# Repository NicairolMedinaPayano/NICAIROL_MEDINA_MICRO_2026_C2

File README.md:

# NICAIROL_MEDINA_MICRO_2026_C2
Repositorio donde iré desarrollando y guardando proyectos y prácticas de microcontroladores, enfocados en programación embebida, automatización y sistemas electrónicos aplicados al área de Mecatrónica. Aquí estarán organizados los códigos, pruebas y avances realizados durante el proceso de aprendizaje y desarrollo.

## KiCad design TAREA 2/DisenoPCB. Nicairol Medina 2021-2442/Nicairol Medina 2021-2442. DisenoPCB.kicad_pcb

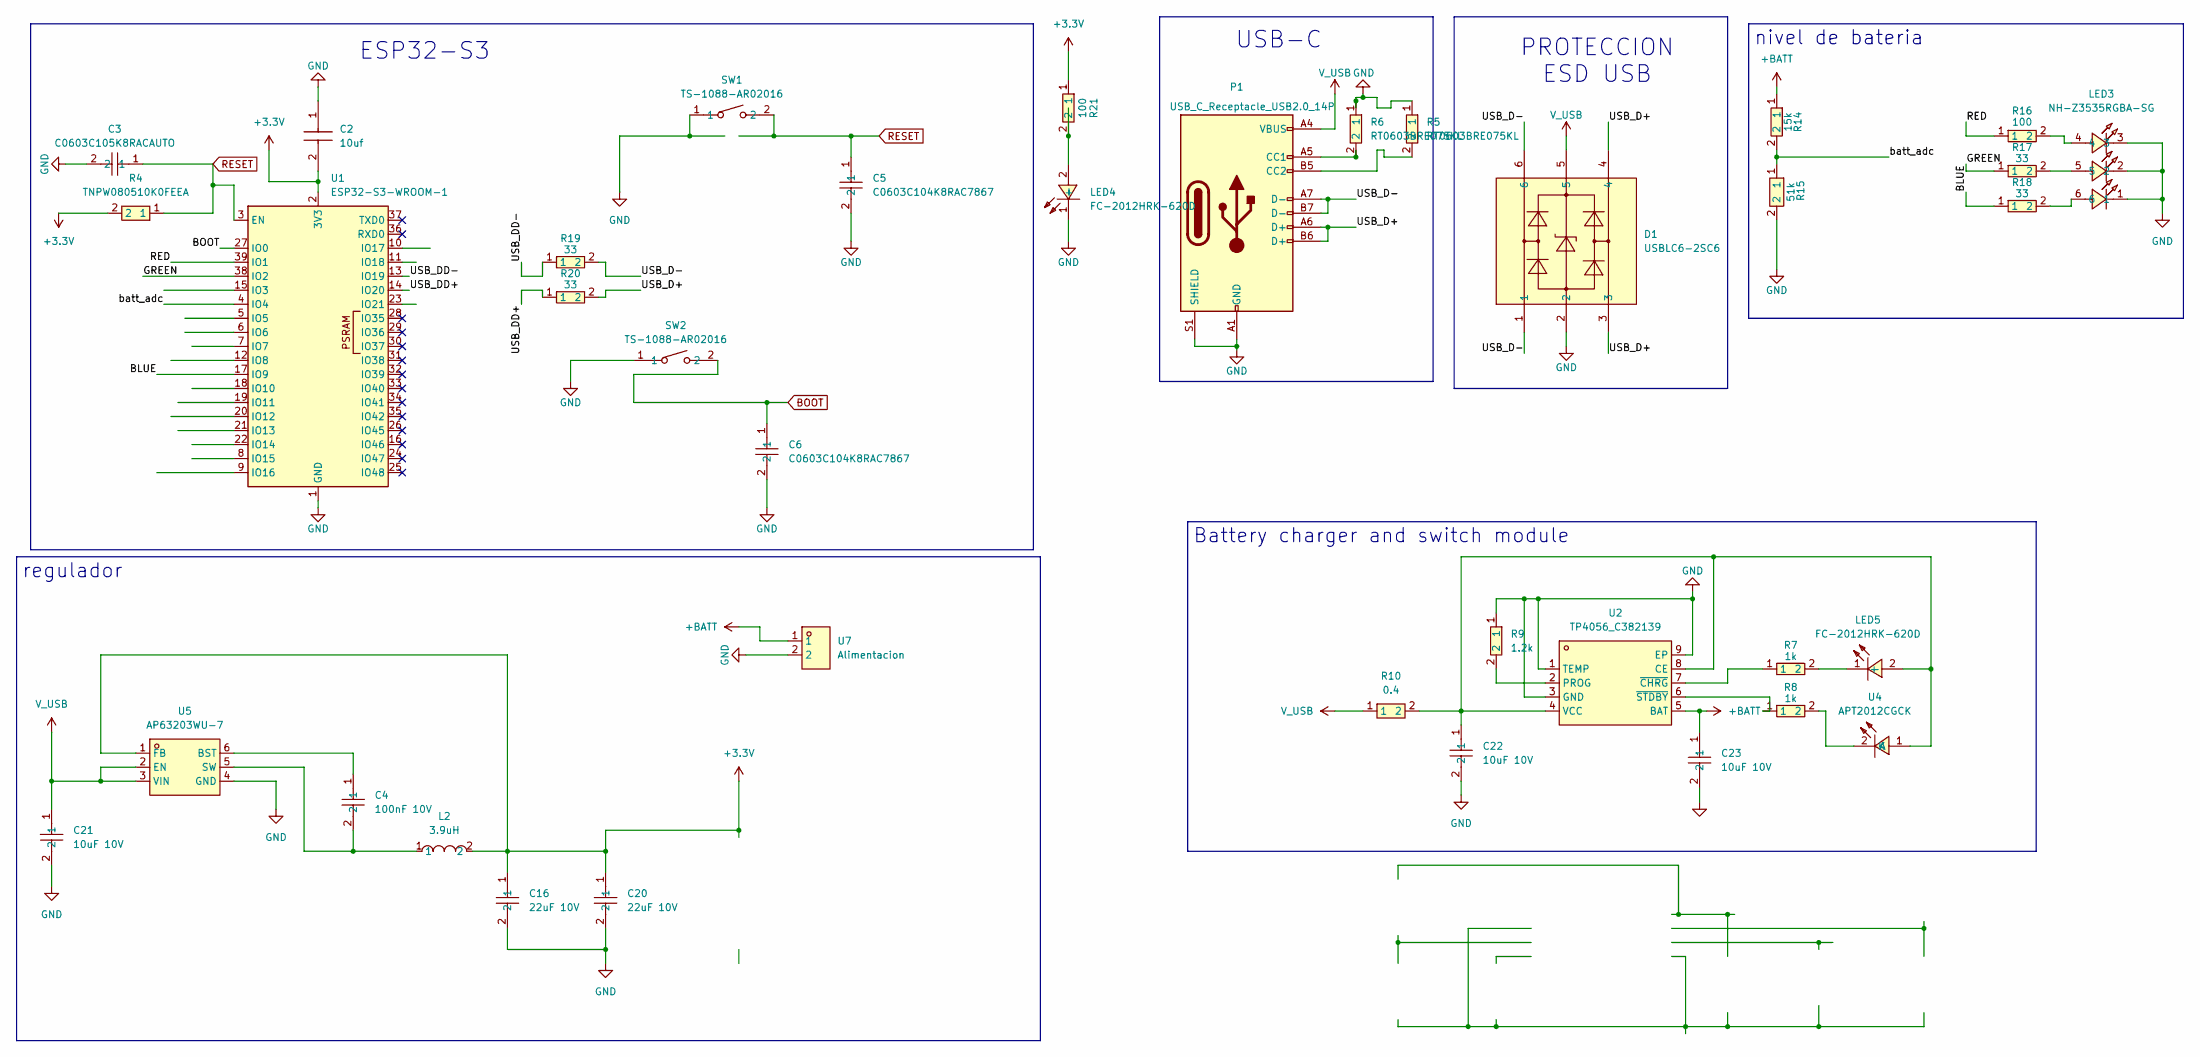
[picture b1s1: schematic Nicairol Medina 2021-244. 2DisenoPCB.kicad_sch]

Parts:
C2: 10uf; C0805; Manufacturer_Part_Number C0805C106M8RACAUTO; Mouser Part Number 80-C0805C106M8RAUTO
C3: C0603C105K8RACAUTO; C0603; MPN C0603C105K8RACAUTO; LCSC Part C2169049
C4: 100nF 10V; C0603; LCSC Part C519438
C5, C6: C0603C104K8RAC7867; C0603; MPN C0603C104K8RAC7867; LCSC Part C599652
C16, C20: 22uF 10V; C0805; LCSC Part C907991
C21, C22, C23: 10uF 10V; C0603; LCSC Part C2959727
D1: USBLC6-2SC6; SOT-23-6_L2.9-W1.6-P0.95-LS2.8-BL; MPN USBLC6-2SC6; LCSC Part C7519
L2: 3.9uH; IND-SMD_TNR4030S-3R9MTF; LCSC Part C42380168
LED3: NH-Z3535RGBA-SG; LED-ARRAY-SMD_6P-L3.7-W3.5-TL-RD; LCSC Part C2874123
LED4, LED5: FC-2012HRK-620D; LED0805-RD; MPN NCD0805R1; LCSC Part C84256
P1: USB_C_Receptacle_USB2.0_14P; USB_C_Receptacle_GCT_USB4105-xx-A_16P_TopMnt_Horizontal
R4: TNPW080510K0FEEA; R0805; MPN TNPW080510K0FEEA; LCSC Part C3013856
R5, R6: RT0603BRE075KL; R0603; MPN RT0603BRE075KL; LCSC Part C862232
R7, R8: 1k; R0603; LCSC Part C22548
R9: 1.2k; R0603; LCSC Part C114605
R10: 0.4; R2512; LCSC Part C5713413
R14: 15k; R0603; LCSC Part C114661
R15: 51k; R0603; LCSC Part C861458
R16, R21: 100; R0603; LCSC Part C105588
R17, R18, R19, R20: 33; R0603; LCSC Part C108661
SW1, SW2: TS-1088-AR02016; SW-SMD_L3.9-W3.0-P4.45; MPN TS-1088-AR02016; LCSC Part C720477
U1: ESP32-S3-WROOM-1
U2: TP4056_C382139; ESOP-8_L4.9-W3.9-P1.27-LS6.0-BL-EP; LCSC Part C382139
U4: APT2012CGCK; LED-SMD_L2.0-W1.3-R-RD; LCSC Part C5875740
U5: AP63203WU-7; TSOT-26_L2.9-W1.6-P0.95-LS2.8-BL; MPN AP63203WU-7; LCSC Part C780769
U7: Alimentacion; CONN-TH_P2.54_KF128-2.54-2P; LCSC Part C474920

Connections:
+3.3V: C2.2, C16.1, C20.1, L2.2, R4.2, R21.1, U1.2 (3V3), U5.1 (FB)
+BATT: C23.1, R14.1, U2.5 (BAT), U7.1
/BLUE: R18.1, U1.17 (IO9)
/GREEN: R17.1, U1.38 (IO2)
/RED: R16.1, U1.39 (IO1)
/USB_D+: D1.3, D1.4, P1.A6 (D+), P1.B6 (D+), R20.2
/USB_D-: D1.1, D1.6, P1.A7 (D-), P1.B7 (D-), R19.2
/USB_DD+: R20.1, U1.14 (IO20)
/USB_DD-: R19.1, U1.13 (IO19)
/batt_adc: R14.2, R15.1, U1.4 (IO4)
BOOT: C6.1, SW2.2, U1.27 (IO0)
GND: C2.1, C3.2, C5.2, C6.2, C16.2, C20.2, C21.2, C22.2, C23.2, D1.2, LED3.1, LED3.2, LED3.3, LED4.1 (-), P1.A1 (GND), P1.A12 (GND), P1.B1 (GND), P1.B12 (GND), P1.S1 (SHIELD), R5.1, R6.1, R9.1, R15.2, SW1.1, SW2.1, U1.1 (GND), U1.40 (GND), U1.41 (GND), U2.1 (TEMP), U2.3 (GND), U2.9 (EP), U5.4 (GND), U7.2
unnamed: LED3.4, R16.2
unnamed: LED3.5, R17.2
unnamed: LED3.6, R18.2
unnamed: LED4.2 (+), R21.2
unnamed: C22.1, LED5.2 (+), R10.2, U2.4 (VCC), U2.8 (CE), U4.1 (A)
unnamed: LED5.1 (-), R7.2
unnamed: P1.A5 (CC1), R6.2
unnamed: P1.B5 (CC2), R5.2
unnamed: R9.2, U2.2 (PROG)
unnamed: R7.1, U2.7 (~CHRG)
unnamed: R8.1, U2.6 (~STDBY)
unnamed: R8.2, U4.2 (K)
unnamed: C4.1, U5.6 (BST)
unnamed: C4.2, L2.1, U5.5 (SW)
RESET: C3.1, C5.1, R4.1, SW1.2, U1.3 (EN)
V_USB: C21.1, D1.5, P1.A4 (VBUS), P1.A9 (VBUS), P1.B4 (VBUS), P1.B9 (VBUS), R10.1, U5.2 (EN), U5.3 (VIN)

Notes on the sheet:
PROTECCION ESD USB
ESP32-S3
USB-C
Battery charger and switch module
nivel de bateria
regulador

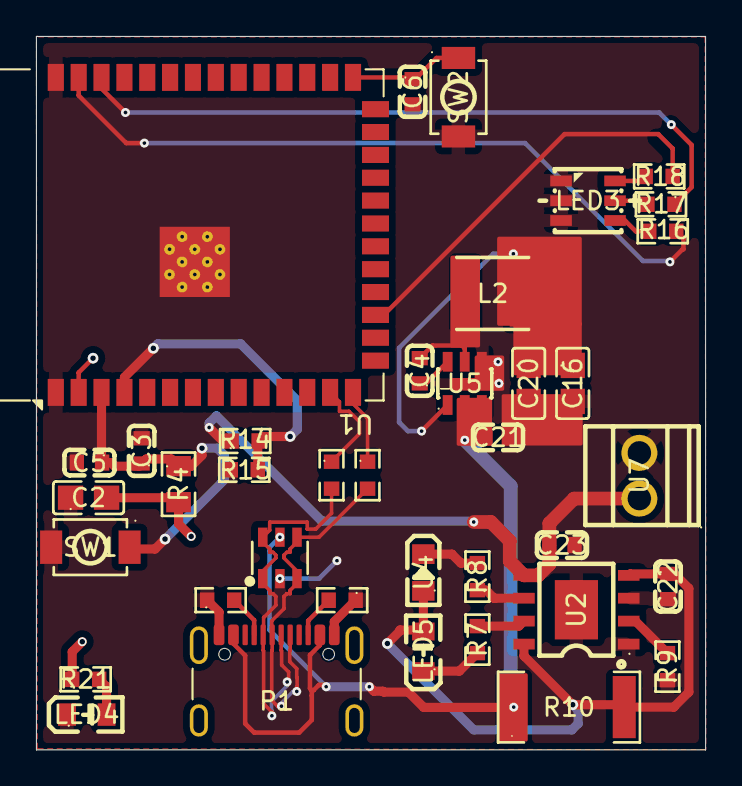
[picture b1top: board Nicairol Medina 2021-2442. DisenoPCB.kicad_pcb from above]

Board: 2 copper layers, 37.2 x 39.6 mm, 38 parts (0 on the bottom side), 28 nets.

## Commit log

2026-05-21 Create bool
